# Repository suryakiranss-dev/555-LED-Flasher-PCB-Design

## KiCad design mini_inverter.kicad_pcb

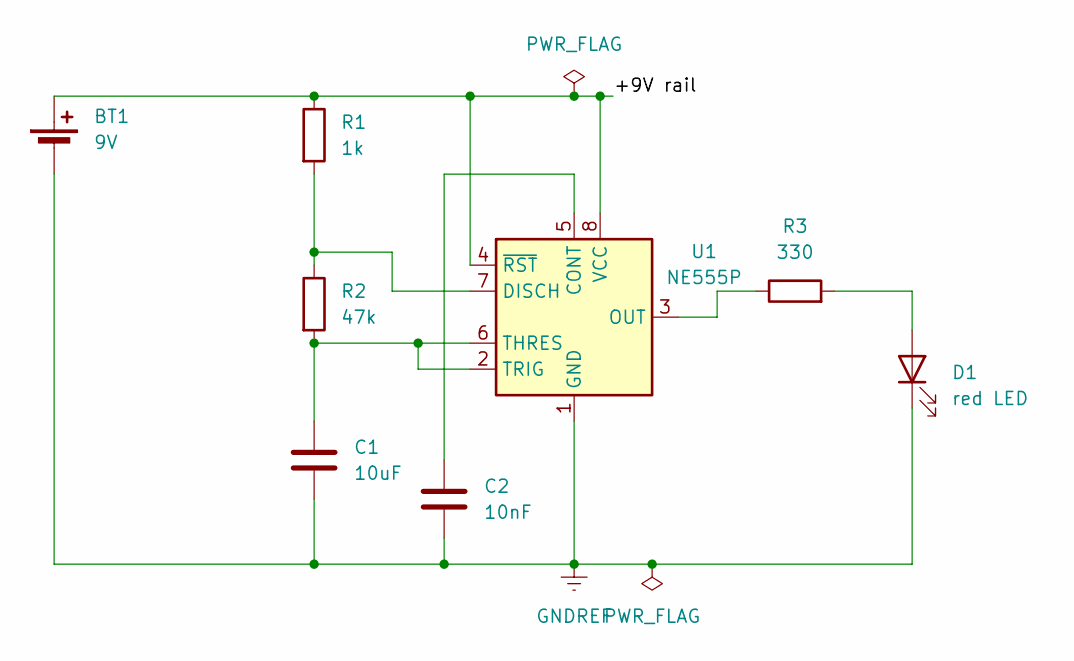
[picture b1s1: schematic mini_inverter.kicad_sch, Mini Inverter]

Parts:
BT1: 9V; PinHeader_1x02_P2.54mm_Vertical
C1: 10uF; CP_Radial_D5.0mm_P2.00mm
C2: 10nF; C_Disc_D3.0mm_W2.0mm_P2.50mm
D1: red LED; LED_D5.0mm
R1: 1k; R_Axial_DIN0207_L6.3mm_D2.5mm_P7.62mm_Horizontal
R2: 47k; R_Axial_DIN0207_L6.3mm_D2.5mm_P7.62mm_Horizontal
R3: 330; R_Axial_DIN0207_L6.3mm_D2.5mm_P7.62mm_Horizontal
U1: NE555P; DIP-8_W7.62mm

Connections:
/+9V rail: BT1.1 (+), R1.1, U1.4 (~RST), U1.8 (VCC)
GNDREF: BT1.2 (-), C1.2, C2.2, D1.1 (K), U1.1 (GND)
unnamed: D1.2 (A), R3.2
unnamed: C2.1, U1.5 (CONT)
unnamed: R1.2, R2.1, U1.7 (DISCH)
unnamed: R3.1, U1.3 (OUT)
unnamed: C1.1, R2.2, U1.2 (TRIG), U1.6 (THRES)

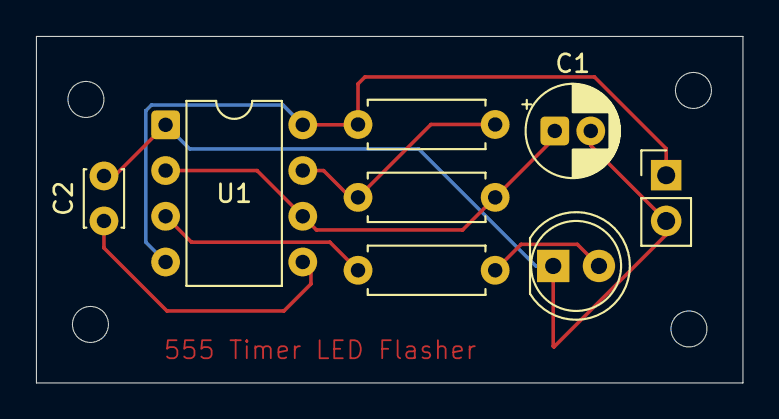
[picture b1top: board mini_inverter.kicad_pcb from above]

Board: 2 copper layers, 39.2 x 19.2 mm, 8 parts (0 on the bottom side), 7 nets.
